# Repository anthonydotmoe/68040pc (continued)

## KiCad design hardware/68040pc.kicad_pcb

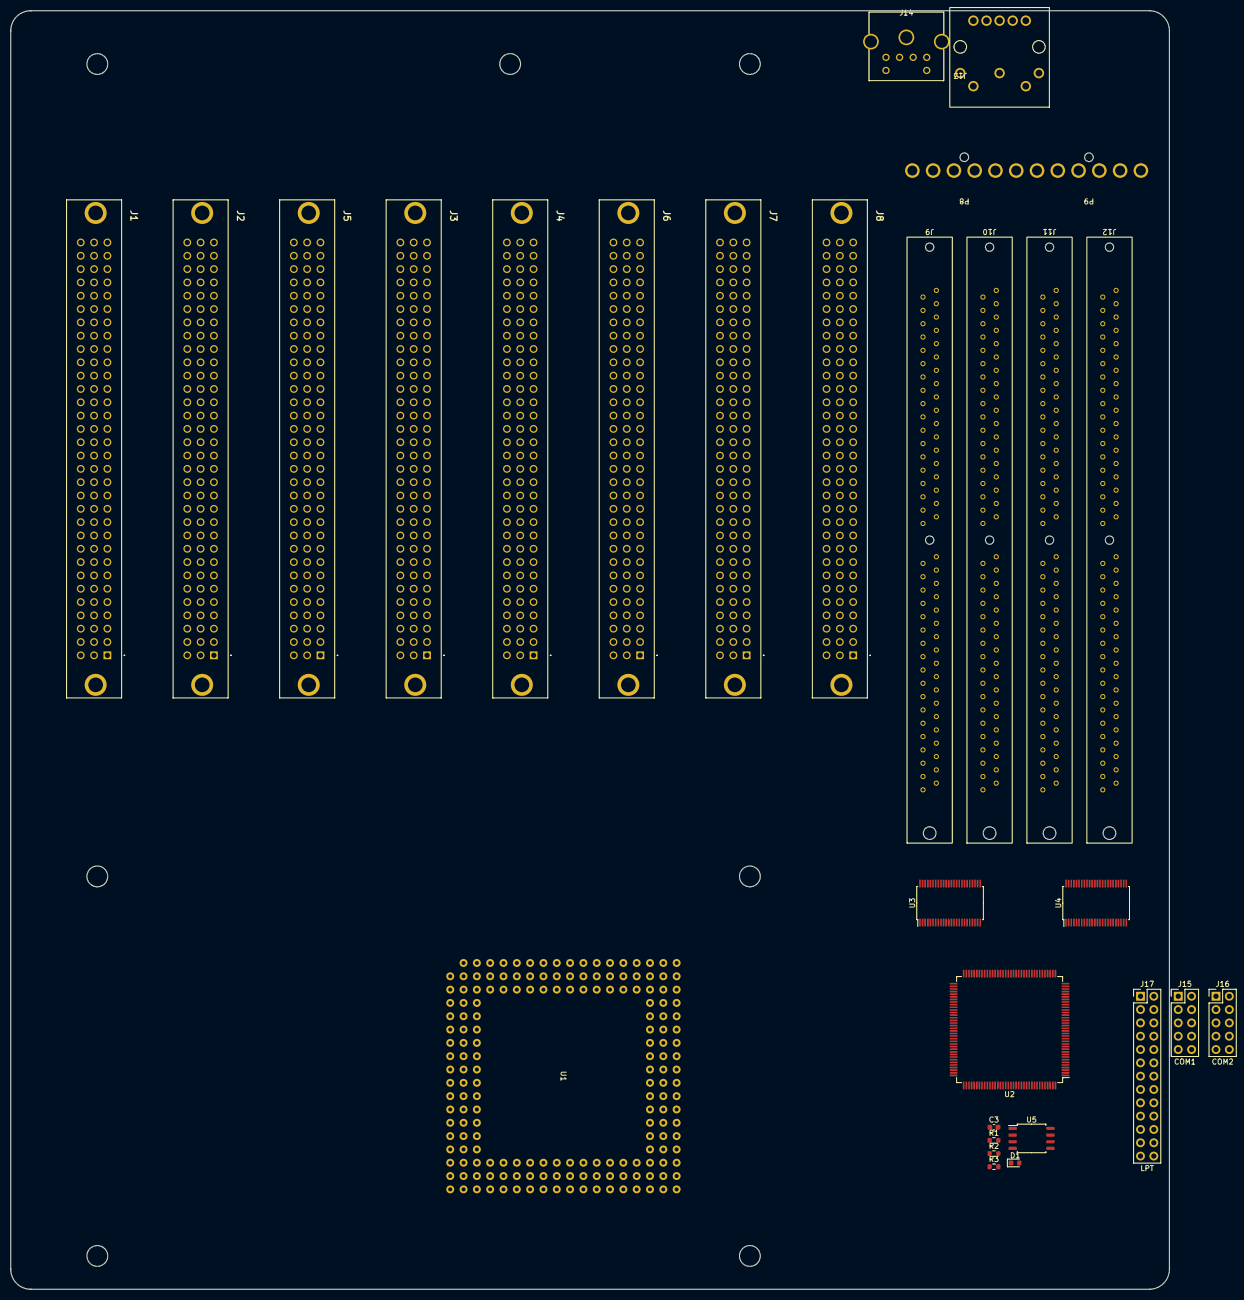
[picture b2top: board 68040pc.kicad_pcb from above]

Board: 4 copper layers, 221.0 x 243.8 mm, 29 parts (0 on the bottom side), 135 nets, no tracks yet.

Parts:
C3: 0.1u; C_0603_1608Metric
D1: LTST-C191KGKT; LED_0603_1608Metric
J1, J2, J3, J4, J5, J6, J7, J8: EXP
J9, J10, J11, J12: SIMM-72
J13: DIN-5_180degree; DIN5-180
J14: Mini-DIN-6; Mini-DIN6
J15: COM1; PinHeader_2x05_P2.54mm_Vertical
J16: COM2; PinHeader_2x05_P2.54mm_Vertical
J17: LPT; PinHeader_2x13_P2.54mm_Vertical
P8, P9: Conn_01x06; 15-48-0106
R1: 2.2K; R_0603_1608Metric
R2, R3: 10K; R_0603_1608Metric
U1: 68LC040; PGA179
U2: ICE40HX4K-TQ144; TQFP-144_20x20mm_P0.5mm
U3, U4: SN74ALVC164245; TSSOP-48_6.1x12.5mm_P0.5mm
U5: W25Q32JVSSIM; SOIC-8_5.23x5.23mm_P1.27mm

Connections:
+3V3: C3.1, J9.10 (VCC), J9.30 (VCC), J9.59 (VCC), J10.10 (VCC), J10.30 (VCC), J10.59 (VCC), J11.10 (VCC), J11.30 (VCC), J11.59 (VCC), J12.10 (VCC), J12.30 (VCC), J12.59 (VCC), R1.2, R2.2, R3.2, U3.31 (VCCA), U3.42 (VCCA), U4.31 (VCCA), U4.42 (VCCA), U5.8 (VCC)
+5V: P8.2, P9.4, P9.5, P9.6, U3.7 (VCCB), U3.18 (VCCB), U4.7 (VCCB), U4.18 (VCCB)
/Expansion/A0: J1.B17, J2.B17, J3.B17, J4.B17, J5.B17, J6.B17, J7.B17, J8.B17, U1.L18 (A0), U2.88 (IOR_137)
/Expansion/A1: J1.A12, J2.A12, J3.A12, J4.A12, J5.A12, J6.A12, J7.A12, J8.A12, U1.K18 (A1), U2.90 (IOR_138)
/Expansion/A2: J1.C12, J2.C12, J3.C12, J4.C12, J5.C12, J6.C12, J7.C12, J8.C12, U1.J17 (A2), U2.91 (IOR_139)
/Expansion/A3: J1.A13, J2.A13, J3.A13, J4.A13, J5.A13, J6.A13, J7.A13, J8.A13, U1.J18 (A3), U2.93 (IOR_140_GBIN3)
/Expansion/A4: J1.C13, J2.C13, J3.C13, J4.C13, J5.C13, J6.C13, J7.C13, J8.C13, U1.H18 (A4), U2.94 (IOR_141_GBIN2)
/Expansion/A5: J1.A14, J2.A14, J3.A14, J4.A14, J5.A14, J6.A14, J7.A14, J8.A14, U1.G18 (A5), U2.95 (IOR_144)
/Expansion/A6: J1.C14, J2.C14, J3.C14, J4.C14, J5.C14, J6.C14, J7.C14, J8.C14, U1.G16 (A6), U2.96 (IOR_146)
/Expansion/A7: J1.A15, J2.A15, J3.A15, J4.A15, J5.A15, J6.A15, J7.A15, J8.A15, U1.F18 (A7), U2.97 (IOR_147)
/Expansion/A8: J1.C15, J2.C15, J3.C15, J4.C15, J5.C15, J6.C15, J7.C15, J8.C15, U1.E18 (A8), U2.98 (IOR_148)
/Expansion/A9: J1.A16, J2.A16, J3.A16, J4.A16, J5.A16, J6.A16, J7.A16, J8.A16, U1.F16 (A9), U2.99 (IOR_152)
/Expansion/A10: J1.C16, J2.C16, J3.C16, J4.C16, J5.C16, J6.C16, J7.C16, J8.C16, U1.P1 (A10), U2.101 (IOR_160)
/Expansion/A11: J1.A17, J2.A17, J3.A17, J4.A17, J5.A17, J6.A17, J7.A17, J8.A17, U1.N3 (A11), U2.102 (IOR_161)
/Expansion/A12: J1.C17, J2.C17, J3.C17, J4.C17, J5.C17, J6.C17, J7.C17, J8.C17, U1.N1 (A12), U2.104 (IOR_164)
/Expansion/A13: J1.A18, J2.A18, J3.A18, J4.A18, J5.A18, J6.A18, J7.A18, J8.A18, U1.M1 (A13), U2.105 (IOR_165)
/Expansion/A14: J1.C18, J2.C18, J3.C18, J4.C18, J5.C18, J6.C18, J7.C18, J8.C18, U1.L1 (A14), U2.106 (IOR_166)
/Expansion/A15: J1.A19, J2.A19, J3.A19, J4.A19, J5.A19, J6.A19, J7.A19, J8.A19, U1.K1 (A15), U2.107 (IOR_167)
/Expansion/A16: J1.C19, J2.C19, J3.C19, J4.C19, J5.C19, J6.C19, J7.C19, J8.C19, U1.K2 (A16), U2.110 (IOT_168)
/Expansion/A17: J1.A20, J2.A20, J3.A20, J4.A20, J5.A20, J6.A20, J7.A20, J8.A20, U1.J1 (A17), U2.112 (IOT_169)
/Expansion/A18: J1.C20, J2.C20, J3.C20, J4.C20, J5.C20, J6.C20, J7.C20, J8.C20, U1.H1 (A18), U2.113 (IOT_170)
/Expansion/A19: J1.A21, J2.A21, J3.A21, J4.A21, J5.A21, J6.A21, J7.A21, J8.A21, U1.J2 (A19), U2.114 (IOT_171)
/Expansion/A20: J1.B18, J2.B18, J3.B18, J4.B18, J5.B18, J6.B18, J7.B18, J8.B18, U1.G1 (A20), U2.115 (IOT_172)
/Expansion/A21: J1.B19, J2.B19, J3.B19, J4.B19, J5.B19, J6.B19, J7.B19, J8.B19, U1.F1 (A21), U2.116 (IOT_173)
/Expansion/A22: J1.B20, J2.B20, J3.B20, J4.B20, J5.B20, J6.B20, J7.B20, J8.B20, U1.E1 (A22), U2.117 (IOT_174)
/Expansion/A23: J1.B21, J2.B21, J3.B21, J4.B21, J5.B21, J6.B21, J7.B21, J8.B21, U1.G3 (A23), U2.118 (IOT_177)
/Expansion/A24: J1.B22, J2.B22, J3.B22, J4.B22, J5.B22, J6.B22, J7.B22, J8.B22, U1.D1 (A24), U2.119 (IOT_178)
/Expansion/A25: J1.B23, J2.B23, J3.B23, J4.B23, J5.B23, J6.B23, J7.B23, J8.B23, U1.F3 (A25), U2.120 (IOT_179)
/Expansion/A26: J1.B24, J2.B24, J3.B24, J4.B24, J5.B24, J6.B24, J7.B24, J8.B24, U1.E2 (A26), U2.121 (IOT_181)
/Expansion/A27: J1.B25, J2.B25, J3.B25, J4.B25, J5.B25, J6.B25, J7.B25, J8.B25, U1.C1 (A27), U2.122 (IOT_190)
/Expansion/A28: J1.B26, J2.B26, J3.B26, J4.B26, J5.B26, J6.B26, J7.B26, J8.B26, U1.E3 (A28), U2.124 (IOT_191)
/Expansion/A29: J1.B27, J2.B27, J3.B27, J4.B27, J5.B27, J6.B27, J7.B27, J8.B27, U1.B1 (A29), U2.125 (IOT_192)
/Expansion/A30: J1.B28, J2.B28, J3.B28, J4.B28, J5.B28, J6.B28, J7.B28, J8.B28, U1.D3 (A30), U2.128 (IOT_197_GBIN1)
/Expansion/A31: J1.B29, J2.B29, J3.B29, J4.B29, J5.B29, J6.B29, J7.B29, J8.B29, U1.A1 (A31), U2.129 (IOT_198_GBIN0)
/Expansion/D0: J1.A3, J2.A3, J3.A3, J4.A3, J5.A3, J6.A3, J7.A3, J8.A3, U1.C3 (D0), U3.2 (1B1)
/Expansion/D1: J1.C3, J2.C3, J3.C3, J4.C3, J5.C3, J6.C3, J7.C3, J8.C3, U1.B3 (D1), U3.3 (1B2)
/Expansion/D2: J1.A4, J2.A4, J3.A4, J4.A4, J5.A4, J6.A4, J7.A4, J8.A4, U1.C4 (D2), U3.5 (1B3)
/Expansion/D3: J1.C4, J2.C4, J3.C4, J4.C4, J5.C4, J6.C4, J7.C4, J8.C4, U1.A2 (D3), U3.6 (1B4)
/Expansion/D4: J1.A5, J2.A5, J3.A5, J4.A5, J5.A5, J6.A5, J7.A5, J8.A5, U1.A3 (D4), U3.8 (1B5)
/Expansion/D5: J1.C5, J2.C5, J3.C5, J4.C5, J5.C5, J6.C5, J7.C5, J8.C5, U1.A4 (D5), U3.9 (1B6)
/Expansion/D6: J1.A6, J2.A6, J3.A6, J4.A6, J5.A6, J6.A6, J7.A6, J8.A6, U1.A5 (D6), U3.11 (1B7)
/Expansion/D7: J1.C6, J2.C6, J3.C6, J4.C6, J5.C6, J6.C6, J7.C6, J8.C6, U1.A6 (D7), U3.12 (1B8)
/Expansion/D8: J1.A7, J2.A7, J3.A7, J4.A7, J5.A7, J6.A7, J7.A7, J8.A7, U1.B7 (D8), U3.13 (2B1)
/Expansion/D9: J1.C7, J2.C7, J3.C7, J4.C7, J5.C7, J6.C7, J7.C7, J8.C7, U1.A7 (D9), U3.14 (2B2)
/Expansion/D10: J1.A8, J2.A8, J3.A8, J4.A8, J5.A8, J6.A8, J7.A8, J8.A8, U1.A8 (D10), U3.16 (2B3)
/Expansion/D11: J1.C8, J2.C8, J3.C8, J4.C8, J5.C8, J6.C8, J7.C8, J8.C8, U1.A9 (D11), U3.17 (2B4)
/Expansion/D12: J1.A9, J2.A9, J3.A9, J4.A9, J5.A9, J6.A9, J7.A9, J8.A9, U1.A10 (D12), U3.19 (2B5)
/Expansion/D13: J1.C9, J2.C9, J3.C9, J4.C9, J5.C9, J6.C9, J7.C9, J8.C9, U1.A11 (D13), U3.20 (2B6)
/Expansion/D14: J1.A10, J2.A10, J3.A10, J4.A10, J5.A10, J6.A10, J7.A10, J8.A10, U1.A12 (D14), U3.22 (2B7)
/Expansion/D15: J1.C10, J2.C10, J3.C10, J4.C10, J5.C10, J6.C10, J7.C10, J8.C10, U1.A13 (D15), U3.23 (2B8)
/Expansion/D16: J1.B1, J2.B1, J3.B1, J4.B1, J5.B1, J6.B1, J7.B1, J8.B1, U1.B11 (D16), U4.2 (1B1)
/Expansion/D17: J1.B2, J2.B2, J3.B2, J4.B2, J5.B2, J6.B2, J7.B2, J8.B2, U1.A14 (D17), U4.3 (1B2)
/Expansion/D18: J1.B3, J2.B3, J3.B3, J4.B3, J5.B3, J6.B3, J7.B3, J8.B3, U1.B12 (D18), U4.5 (1B3)
/Expansion/D19: J1.B4, J2.B4, J3.B4, J4.B4, J5.B4, J6.B4, J7.B4, J8.B4, U1.A15 (D19), U4.6 (1B4)
/Expansion/D20: J1.B5, J2.B5, J3.B5, J4.B5, J5.B5, J6.B5, J7.B5, J8.B5, U1.A16 (D20), U4.8 (1B5)
/Expansion/D21: J1.B6, J2.B6, J3.B6, J4.B6, J5.B6, J6.B6, J7.B6, J8.B6, U1.A17 (D21), U4.9 (1B6)
/Expansion/D22: J1.B7, J2.B7, J3.B7, J4.B7, J5.B7, J6.B7, J7.B7, J8.B7, U1.B16 (D22), U4.11 (1B7)
/Expansion/D23: J1.B8, J2.B8, J3.B8, J4.B8, J5.B8, J6.B8, J7.B8, J8.B8, U1.C15 (D23), U4.12 (1B8)
/Expansion/D24: J1.B9, J2.B9, J3.B9, J4.B9, J5.B9, J6.B9, J7.B9, J8.B9, U1.A18 (D24), U4.13 (2B1)
/Expansion/D25: J1.B10, J2.B10, J3.B10, J4.B10, J5.B10, J6.B10, J7.B10, J8.B10, U1.C16 (D25), U4.14 (2B2)
/Expansion/D26: J1.B11, J2.B11, J3.B11, J4.B11, J5.B11, J6.B11, J7.B11, J8.B11, U1.B18 (D26), U4.16 (2B3)
/Expansion/D27: J1.B12, J2.B12, J3.B12, J4.B12, J5.B12, J6.B12, J7.B12, J8.B12, U1.D16 (D27), U4.17 (2B4)
/Expansion/D28: J1.B13, J2.B13, J3.B13, J4.B13, J5.B13, J6.B13, J7.B13, J8.B13, U1.C18 (D28), U4.19 (2B5)
/Expansion/D29: J1.B14, J2.B14, J3.B14, J4.B14, J5.B14, J6.B14, J7.B14, J8.B14, U1.E16 (D29), U4.20 (2B6)
/Expansion/D30: J1.B15, J2.B15, J3.B15, J4.B15, J5.B15, J6.B15, J7.B15, J8.B15, U1.E17 (D30), U4.22 (2B7)
/Expansion/D31: J1.B16, J2.B16, J3.B16, J4.B16, J5.B16, J6.B16, J7.B16, J8.B16, U1.D18 (D31), U4.23 (2B8)
/GND_{L}: U1.C6 (GND), U1.C7 (GND), U1.C9 (GND), U1.C11 (GND), U1.C13 (GND), U1.K3 (GND), U1.K16 (GND), U1.L3 (GND), U1.M16 (GND), U1.R4 (GND), U1.R11 (GND), U1.R13 (GND), U1.S10 (GND), U1.T4 (GND)
/GND_{O}: U1.B2 (GND), U1.B4 (GND), U1.B6 (GND), U1.B8 (GND), U1.B10 (GND), U1.B13 (GND), U1.B15 (GND), U1.B17 (GND), U1.D2 (GND), U1.D17 (GND), U1.F2 (GND), U1.F17 (GND), U1.H2 (GND), U1.H17 (GND), U1.L2 (GND), U1.L17 (GND), U1.N2 (GND), U1.N17 (GND), U1.Q2 (GND), U1.Q17 (GND), U1.S2 (GND), U1.S15 (GND), U1.S17 (GND)
/GND_{P}: U1.R6 (GND), U1.R10 (GND), U1.S9 (GND)
/Memory/CDONE: D1.2 (A), R1.1, U2.65 (CDONE)
/Memory/DRAM_A0: J9.12 (A0), J10.12 (A0), J11.12 (A0), J12.12 (A0), U2.37 (IOB_56)
/Memory/DRAM_A1: J9.13 (A1), J10.13 (A1), J11.13 (A1), J12.13 (A1), U2.38 (IOB_57)
/Memory/DRAM_A2: J9.14 (A2), J10.14 (A2), J11.14 (A2), J12.14 (A2), U2.39 (IOB_61)
/Memory/DRAM_A3: J9.15 (A3), J10.15 (A3), J11.15 (A3), J12.15 (A3), U2.41 (IOB_63)
/Memory/DRAM_A4: J9.16 (A4), J10.16 (A4), J11.16 (A4), J12.16 (A4), U2.42 (IOB_64)
/Memory/DRAM_A5: J9.17 (A5), J10.17 (A5), J11.17 (A5), J12.17 (A5), U2.43 (IOB_71)
/Memory/DRAM_A6: J9.18 (A6), J10.18 (A6), J11.18 (A6), J12.18 (A6), U2.44 (IOB_72)
/Memory/DRAM_A7: J9.28 (A7), J10.28 (A7), J11.28 (A7), J12.28 (A7), U2.47 (IOB_79)
/Memory/DRAM_A8: J9.31 (A8), J10.31 (A8), J11.31 (A8), J12.31 (A8), U2.49 (IOB_81_GBIN5)
/Memory/DRAM_A9: J9.32 (A9), J10.32 (A9), J11.32 (A9), J12.32 (A9), U2.52 (IOB_82_GBIN4)
/Memory/DRAM_A10: J9.19 (A10), J10.19 (A10), J11.19 (A10), J12.19 (A10), U2.45 (IOB_73)
/Memory/DRAM_A11: J9.29 (A11), J10.29 (A11), J11.29 (A11), J12.29 (A11), U2.48 (IOB_80)
/Memory/DRAM_BUF_DIR: U3.1 (1DIR), U3.24 (2DIR), U4.1 (1DIR), U4.24 (2DIR)
/Memory/DRAM_BUF_~OE: U3.25 (*2OE), U3.48 (*1OE), U4.25 (*2OE), U4.48 (*1OE)
/Memory/DRAM_D0: J9.2 (DQ0), J10.2 (DQ0), J11.2 (DQ0), J12.2 (DQ0), U3.47 (1A1)
/Memory/DRAM_D1: J9.4 (DQ1), J10.4 (DQ1), J11.4 (DQ1), J12.4 (DQ1), U3.46 (1A2)
/Memory/DRAM_D2: J9.6 (DQ2), J10.6 (DQ2), J11.6 (DQ2), J12.6 (DQ2), U3.44 (1A3)
/Memory/DRAM_D3: J9.8 (DQ3), J10.8 (DQ3), J11.8 (DQ3), J12.8 (DQ3), U3.43 (1A4)
/Memory/DRAM_D4: J9.20 (DQ4), J10.20 (DQ4), J11.20 (DQ4), J12.20 (DQ4), U3.41 (1A5)
/Memory/DRAM_D5: J9.22 (DQ5), J10.22 (DQ5), J11.22 (DQ5), J12.22 (DQ5), U3.40 (1A6)
/Memory/DRAM_D6: J9.24 (DQ6), J10.24 (DQ6), J11.24 (DQ6), J12.24 (DQ6), U3.38 (1A7)
/Memory/DRAM_D7: J9.26 (DQ7), J10.26 (DQ7), J11.26 (DQ7), J12.26 (DQ7), U3.37 (1A8)
/Memory/DRAM_D8: J9.49 (DQ8), J10.49 (DQ8), J11.49 (DQ8), J12.49 (DQ8), U3.36 (2A1)
/Memory/DRAM_D9: J9.51 (DQ9), J10.51 (DQ9), J11.51 (DQ9), J12.51 (DQ9), U3.35 (2A2)
/Memory/DRAM_D10: J9.53 (DQ10), J10.53 (DQ10), J11.53 (DQ10), J12.53 (DQ10), U3.33 (2A3)
/Memory/DRAM_D11: J9.55 (DQ11), J10.55 (DQ11), J11.55 (DQ11), J12.55 (DQ11), U3.32 (2A4)
/Memory/DRAM_D12: J9.57 (DQ12), J10.57 (DQ12), J11.57 (DQ12), J12.57 (DQ12), U3.30 (2A5)
/Memory/DRAM_D13: J9.61 (DQ13), J10.61 (DQ13), J11.61 (DQ13), J12.61 (DQ13), U3.29 (2A6)
/Memory/DRAM_D14: J9.63 (DQ14), J10.63 (DQ14), J11.63 (DQ14), J12.63 (DQ14), U3.27 (2A7)
/Memory/DRAM_D15: J9.65 (DQ15), J10.65 (DQ15), J11.65 (DQ15), J12.65 (DQ15), U3.26 (2A8)
/Memory/DRAM_D16: J9.3 (DQ16), J10.3 (DQ16), J11.3 (DQ16), J12.3 (DQ16), U4.47 (1A1)
/Memory/DRAM_D17: J9.5 (DQ17), J10.5 (DQ17), J11.5 (DQ17), J12.5 (DQ17), U4.46 (1A2)
/Memory/DRAM_D18: J9.7 (DQ18), J10.7 (DQ18), J11.7 (DQ18), J12.7 (DQ18), U4.44 (1A3)
/Memory/DRAM_D19: J9.9 (DQ19), J10.9 (DQ19), J11.9 (DQ19), J12.9 (DQ19), U4.43 (1A4)
/Memory/DRAM_D20: J9.21 (DQ20), J10.21 (DQ20), J11.21 (DQ20), J12.21 (DQ20), U4.41 (1A5)
/Memory/DRAM_D21: J9.23 (DQ21), J10.23 (DQ21), J11.23 (DQ21), J12.23 (DQ21), U4.40 (1A6)
/Memory/DRAM_D22: J9.25 (DQ22), J10.25 (DQ22), J11.25 (DQ22), J12.25 (DQ22), U4.38 (1A7)
/Memory/DRAM_D23: J9.27 (DQ23), J10.27 (DQ23), J11.27 (DQ23), J12.27 (DQ23), U4.37 (1A8)
/Memory/DRAM_D24: J9.50 (DQ24), J10.50 (DQ24), J11.50 (DQ24), J12.50 (DQ24), U4.36 (2A1)
/Memory/DRAM_D25: J9.52 (DQ25), J10.52 (DQ25), J11.52 (DQ25), J12.52 (DQ25), U4.35 (2A2)
/Memory/DRAM_D26: J9.54 (DQ26), J10.54 (DQ26), J11.54 (DQ26), J12.54 (DQ26), U4.33 (2A3)
/Memory/DRAM_D27: J9.56 (DQ27), J10.56 (DQ27), J11.56 (DQ27), J12.56 (DQ27), U4.32 (2A4)
/Memory/DRAM_D28: J9.58 (DQ28), J10.58 (DQ28), J11.58 (DQ28), J12.58 (DQ28), U4.30 (2A5)
/Memory/DRAM_D29: J9.60 (DQ29), J10.60 (DQ29), J11.60 (DQ29), J12.60 (DQ29), U4.29 (2A6)
/Memory/DRAM_D30: J9.62 (DQ30), J10.62 (DQ30), J11.62 (DQ30), J12.62 (DQ30), U4.27 (2A7)
/Memory/DRAM_D31: J9.64 (DQ31), J10.64 (DQ31), J11.64 (DQ31), J12.64 (DQ31), U4.26 (2A8)
/Memory/DRAM_R/~W: J9.47 (R/~W), J10.47 (R/~W), J11.47 (R/~W), J12.47 (R/~W)
/Memory/FLASH_MISO: U2.68 (IOB_106_SDI), U5.2 (DO(IO1))
/Memory/FLASH_MOSI: U2.67 (IOB_105_SDO), U5.5 (DI(IO0))
/Memory/FLASH_SCK: R3.1, U2.70 (IOB_107_SCK), U5.6 (CLK)
/Memory/FLASH_SS: R2.1, U2.71 (IOB_108_SS), U5.1 (~CS)
/Memory/~RAS0: J9.44 (~RAS0), J10.44 (~RAS0), J11.44 (~RAS0), J12.44 (~RAS0), U2.60 (IOB_95)
/Memory/~RAS1: J9.45 (~RAS1), J10.45 (~RAS1), J11.45 (~RAS1), J12.45 (~RAS1), U2.61 (IOB_96)
/Memory/~RAS2: J9.34 (~RAS2), J10.34 (~RAS2), J11.34 (~RAS2), J12.34 (~RAS2), U2.56 (IOB_94)
/Memory/~RAS3: J9.33 (~RAS3), J10.33 (~RAS3), J11.33 (~RAS3), J12.33 (~RAS3), U2.55 (IOB_91)
/V_{CC}_{L}: U1.C5 (V_{CC}), U1.C8 (V_{CC}), U1.C10 (V_{CC}), U1.C12 (V_{CC}), U1.C14 (V_{CC}), U1.H3 (V_{CC}), U1.H16 (V_{CC}), U1.J3 (V_{CC}), U1.J16 (V_{CC}), U1.L16 (V_{CC}), U1.M3 (V_{CC}), U1.R5 (V_{CC}), U1.R12 (V_{CC})
/V_{CC}_{O}: U1.B5 (V_{CC}), U1.B9 (V_{CC}), U1.B14 (V_{CC}), U1.C2 (V_{CC}), U1.C17 (V_{CC}), U1.G2 (V_{CC}), U1.G17 (V_{CC}), U1.M2 (V_{CC}), U1.M17 (V_{CC}), U1.R2 (V_{CC}), U1.R17 (V_{CC}), U1.S16 (V_{CC})
/V_{CC}_{P}: U1.R8 (V_{CC}), U1.S8 (V_{CC})
GND: C3.2, D1.1 (K), J1.MH, J2.MH, J3.MH, J4.MH, J5.MH, J6.MH, J7.MH, J8.MH, J9.1 (GND), J9.39 (GND), J9.72 (GND), J10.1 (GND), J10.39 (GND), J10.72 (GND), J11.1 (GND), J11.39 (GND), J11.72 (GND), J12.1 (GND), J12.39 (GND), J12.72 (GND), J13.4, J14.3, J15.5, J16.5, J17.10, J17.12, J17.14, J17.16, J17.18, J17.20, J17.22, J17.26, P8.5, P8.6, P9.1, P9.2, U3.4 (GND), U3.10 (GND), U3.15 (GND), U3.21 (GND), U3.28 (GND), U3.34 (GND), U3.39 (GND), U3.45 (GND), U4.4 (GND), U4.10 (GND), U4.15 (GND), U4.21 (GND), U4.28 (GND), U4.34 (GND), U4.39 (GND), U4.45 (GND), U5.4 (GND)
unnamed: U2.123 (VCCIO_0), U2.131 (VCCIO_0)
unnamed: U2.89 (VCCIO_1), U2.100 (VCCIO_1)
unnamed: U2.46 (VCCIO_2), U2.57 (VCCIO_2)
unnamed: U2.6 (VCCIO_3), U2.30 (VCCIO_3)
unnamed: U2.5 (GND), U2.13 (GND), U2.14 (GND), U2.59 (GND), U2.69 (GND), U2.86 (GND), U2.103 (GND), U2.132 (GND), U2.140 (GND)
unnamed: U2.27 (VCC), U2.40 (VCC), U2.92 (VCC), U2.111 (VCC)

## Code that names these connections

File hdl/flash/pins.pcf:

set_io	clk		94
set_frequency clk	33
set_io	rst		52
set_io	led		95
set_io	btn		93

set_io	dbg1		60
set_io	dbg2		62
set_io	dbg3		61

set_io	spi_mosi	67
set_io	spi_miso	68
set_io	spi_sck		70
set_io	spi_ss		71
set_io	spi_io2		64
set_io	spi_io3		63

set_io	d_dir		110
set_io	d_oe		112

set_io	ts		45
set_io	tip		47
set_io	tbi		31
set_io	tci		32
set_io	tea		33
set_io	ta		34

set_io	tt[0]		49
set_io	tt[1]		48

set_io	tm[0]		41
set_io	tm[1]		39
set_io	tm[2]		38

set_io	IPL[0]		98
set_io	IPL[1]		99
set_io	IPL[2]		101

set_io	rw		44
set_io	siz[0]		43
set_io	siz[1]		42

set_io	DSACK[0]	96
set_io	DSACK[1]	97
set_io	RESIZ_CS	104
set_io	RESIZ_DS	56

set_io	COM_CS		102
set_io	COM_IRQ		55
set_io	COM_IACK	105
set_io	RAM_CS		106
set_io	AVEC		107

set_io	a[0]		91
set_io	a[1]		90
set_io	a[2]		88
set_io	a[3]		87
set_io	a[4]		85
set_io	a[5]		84
set_io	a[6]		82
set_io	a[7]		83
set_io	a[8]		10
set_io	a[9]		11
set_io	a[10]		29
set_io	a[11]		28
set_io	a[12]		26
set_io	a[13]		25
set_io	a[14]		24
set_io	a[15]		22
set_io	a[16]		23
set_io	a[17]		21
set_io	a[18]		18
set_io	a[19]		19
set_io	a[20]		16
set_io	a[21]		12
set_io	a[22]		81
set_io	a[23]		17
set_io	a[24]		78
set_io	a[25]		15
set_io	a[26]		80
set_io	a[27]		75
set_io	a[28]		79
set_io	a[29]		74
set_io	a[30]		76
set_io	a[31]		73

set_io 	d[0]		138
set_io 	d[1]		136
set_io 	d[2]		139
set_io 	d[3]		135
set_io 	d[4]		137
set_io 	d[5]		141
set_io 	d[6]		142
set_io 	d[7]		143
set_io 	d[8]		144
set_io 	d[9]		1
set_io 	d[10]		2
set_io 	d[11]		3
set_io 	d[12]		4
set_io 	d[13]		7
set_io 	d[14]		8
set_io 	d[15]		9
set_io 	d[16]		134
set_io 	d[17]		130
set_io 	d[18]		129
set_io 	d[19]		128
set_io 	d[20]		125
set_io 	d[21]		124
set_io 	d[22]		122
set_io 	d[23]		121
set_io 	d[24]		120
set_io 	d[25]		119
set_io 	d[26]		118
set_io 	d[27]		117
set_io 	d[28]		116
set_io 	d[29]		115
set_io 	d[30]		114
set_io 	d[31]		113

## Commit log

2023-08-22 rough draft 68040 symbol, pga179 footprint
2023-08-22 add rough draft SIMM-72 symbol/footprint
2023-08-25 fix symbols/footprints
2023-08-25 add atx outline, begin DRAM schematic
2023-08-26 more memory wiring
2023-08-27 lock position of expansion slots
2023-08-28 add memory map plan
2023-08-29 start documenting
2023-08-29 make my own 3D models for connectors
2023-08-29 fix slot orientation (slot 1 only)\nTodo.. fix other slots
2023-09-01 fix EXP connector positioning
2023-09-10 Add 3d models, re-place exp slots, add components
2023-09-12 fill in documentation
2023-09-22 jot down more ideas
2023-09-25 more ideas, add motherboard drawing draft
2023-10-23 update gitignore
2023-10-23 start on FPGA work
2023-10-23 resize board to Baby-AT
2023-10-24 Fix syntax
2023-10-29 dram
2023-10-29 create transfer SIZ/A to CAS/RAS decoder
2023-10-29 settled addressing scheme
2023-10-29 Add README.md
2023-10-30 change memory map, add SIMM layout table
2023-10-30 add initialization delay for DRAM chips
2023-10-31 DRAM controller progress
2023-11-14 reformat expanison port symbol
2023-11-14 reconfigure expansion slot schematic
2023-11-27 begin work on a simpler first draft board
2023-12-09 update cpu symbol, topology
2023-12-10 add interrupt logic, clean up modules
2023-12-14 Start writing firmware
2023-12-14 make documentation at least a little better
2023-12-18 getting closer
2023-12-22 re-design level shifters
2024-02-25 restructure, create minimum board project
2024-02-26 work on testboard, move 3d models
2024-02-27 work on testboard
2024-02-27 root mostly finished
2024-03-04 start new rom for simpleboard
2024-03-04 simpleboard nearly complete
2024-03-05 fix linkage symbol bug
2024-03-06 fix up FPGA pinning
2024-03-06 I ripped it all apart
2024-03-09 pinouts
2024-03-09 layout
2024-03-10 testboard - schematic and route done
2024-03-11 create BOM, still needs more
2024-03-13 make 3.3v reg bigger
2024-03-13 more POST changes
2024-03-14 layout FTDI
2024-03-15 finish routing testboard
2024-03-15 remove duplicate LV_A0 track
2024-03-16 Gerbers published, board out for production!
2024-03-17 restructure firmware directory, update makefile
2024-03-19 make vector table initialization more portable
2024-03-20 fix interrupt checks, create stack-free putc/puts
2024-03-20 remove *.asc files from commits
2024-03-24 update errata for testboard
2024-03-24 initial commit: reading flash through FPGA
2024-03-26 trying to get the flash to wake up
2024-03-27 remove apio, remove flash sleep command from bitstream
2024-03-27 flash reading now!
2024-03-29 Move UART init up and write test char
2024-03-29 start integrating UART & RAM
2024-03-29 add pulseview layout
2024-03-31 Fiddle with 68150 select (RAM seems working now)
2024-04-01 rename "flash" dir
2024-04-01 skip memory test to observe functionality
2024-04-02 hasty interrupt button addition
2024-04-02 Re-integrate memory test, add register dump to vectors
2024-04-02 mock-up POST summary screen
2024-04-02 stop rom binary from being tracked
2024-04-02 fix SR dump, trying to get rte working
2024-04-03 start implementing circular buffer for uart
2024-04-04 add printf source repository
2024-04-04 move -I statement
2024-04-04 add volatile
2024-04-04 printf working with tx circular buffer
2024-04-04 add interrupt path for UART
2024-04-04 fix vector move logic (moveq sign extends)
2024-04-08 start separating modules
2024-04-22 Separate ROM state-machine
2024-05-04 create interrupt module
2024-05-07 commit to save this version of interrupt interface
2024-05-07 interrupt peripheral works, need to adjust firmware
2024-05-13 fix firmware interrupt test
2024-05-19 add receive support to uart
2025-03-01 Dump WIP files from laptop
2025-03-02 trying to get uart to work properly
2025-03-21 start work on moving to new link method based on work from tomstorey/m68k_bare_metal
2026-01-18 vscode fixes
2026-01-18 integrate startup code to zero bss (_startup.c), copy init data. switch to building elf->bin. alter memory map. still troubleshooting DUART.
2026-01-20 link.ld: replace forgotten (NOLOAD) on .bss
2026-01-31 fix incorrect sp restore; use `stop` to die
2026-01-31 implement ELF loading routines to copy OS image from ROM to RAM and jump
2026-02-13 rename bootinfo to bootparams
2026-02-13 finish rename bootinfo to bootparams
2026-02-13 load userimage into RAM for kernel
2026-02-13 embed userimage
2026-05-03 Codex: Straighten out FPGA address decode/select logic.
2026-05-03 make the LED CPU controllable
2026-05-04 update notes
2026-05-04 add simple TX-only UART peripheral
2026-05-04 add FPGA UART RX
2026-05-04 convert tabs to spaces
2026-05-05 reorganize FPGA stuff
